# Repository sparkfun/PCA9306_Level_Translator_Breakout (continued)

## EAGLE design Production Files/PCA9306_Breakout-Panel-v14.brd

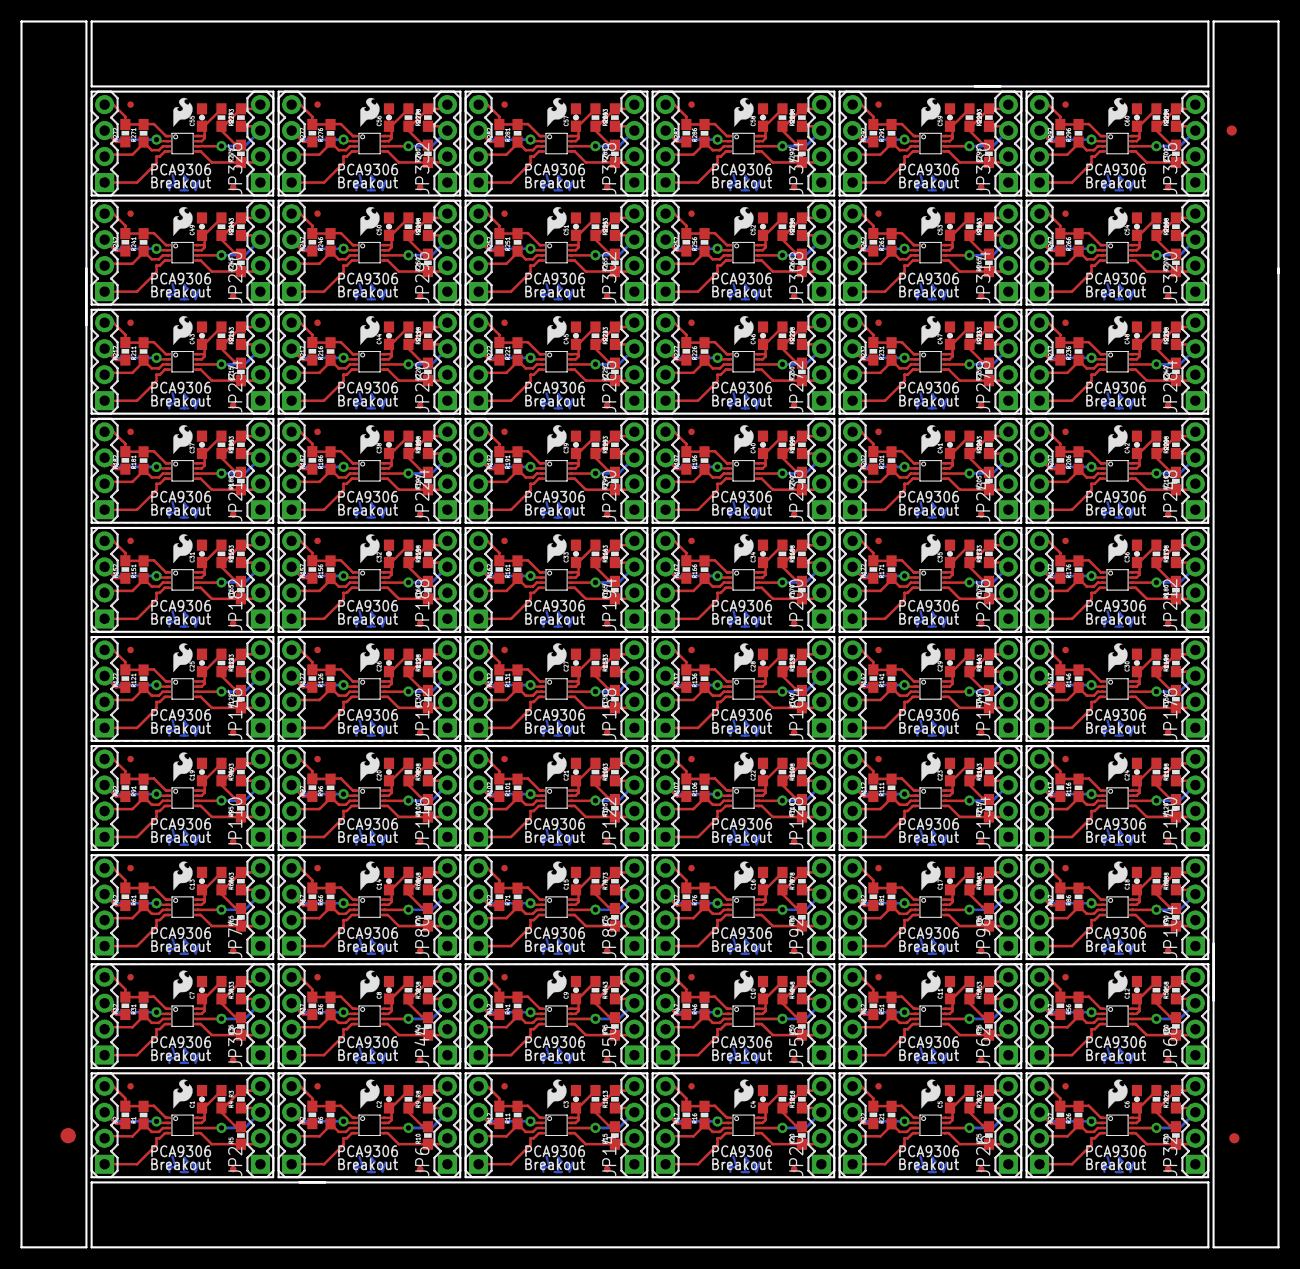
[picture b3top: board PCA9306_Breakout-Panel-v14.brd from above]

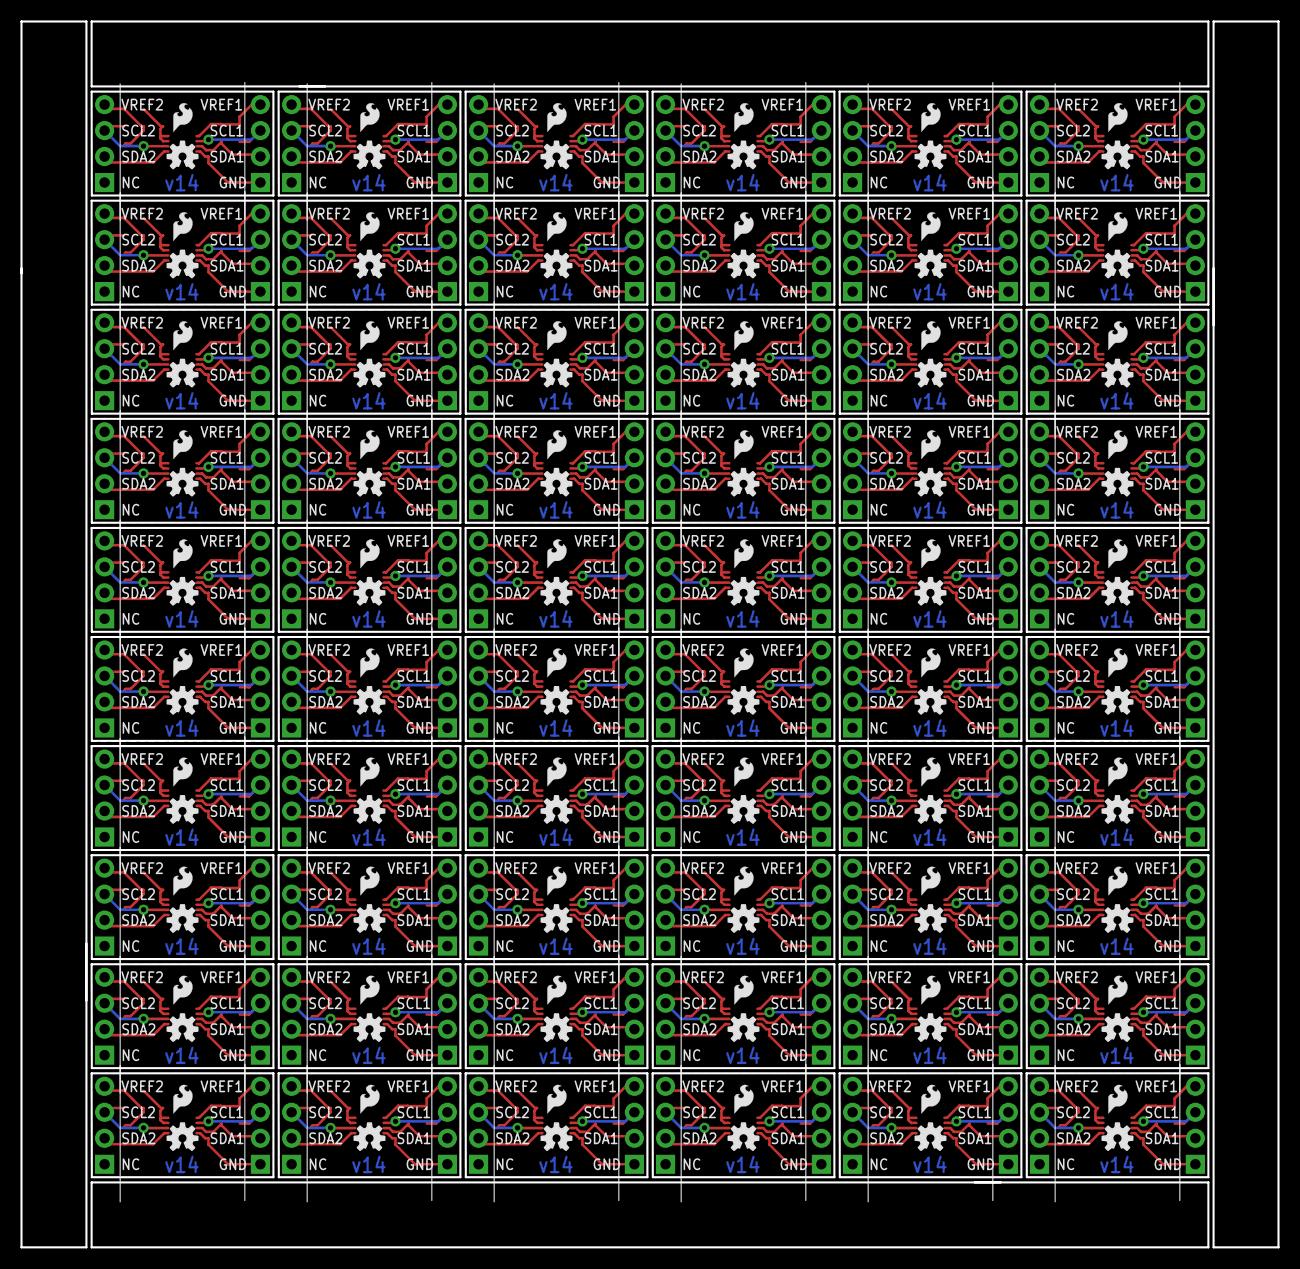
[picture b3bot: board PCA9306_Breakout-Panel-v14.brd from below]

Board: 2 copper layers, 122.9 x 119.9 mm, 843 parts (120 on the bottom side), 480 nets.

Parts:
C1, C2, C3, C4, C5, C6, C7, C8, C9, C10, C11, C12, C13, C14, C15, C16, C17, C18, C19, C20, C21, C22, C23, C24, C25, C26, C27, C28, C29, C30, C31, C32, C33, C34, C35, C36, C37, C38, C39, C40, C41, C42, C43, C44, C45, C46, C47, C48, C49, C50, C51, C52, C53, C54, C55, C56, C57, C58, C59, C60: 0.1uF; 0603-CAP
E$1: FIDUCIAL-1.5X3
E$4, E$5: FIDUCIAL-1X2
JP1, JP2, JP5, JP6, JP13, JP14, JP19, JP20, JP25, JP26, JP31, JP32, JP37, JP38, JP43, JP44, JP49, JP50, JP55, JP56, JP61, JP62, JP67, JP68, JP73, JP74, JP79, JP80, JP85, JP86, JP91, JP92, JP97, JP98, JP103, JP104, JP109, JP110, JP115, JP116, JP121, JP122, JP127, JP128, JP133, JP134, JP139, JP140, JP145, JP146, JP151, JP152, JP157, JP158, JP163, JP164, JP169, JP170, JP175, JP176, JP181, JP182, JP187, JP188, JP193, JP194, JP199, JP200, JP205, JP206, JP211, JP212, JP217, JP218, JP223, JP224, JP229, JP230, JP235, JP236, JP241, JP242, JP247, JP248, JP253, JP254, JP259, JP260, JP265, JP266, JP271, JP272, JP277, JP278, JP283, JP284, JP289, JP290, JP295, JP296, JP301, JP302, JP307, JP308, JP313, JP314, JP319, JP320, JP325, JP326, JP331, JP332, JP337, JP338, JP343, JP344, JP349, JP350, JP355, JP356: 1X04
JP3, JP4, JP9, JP10, JP15, JP16, JP21, JP22, JP27, JP28, JP33, JP34, JP39, JP40, JP45, JP46, JP51, JP52, JP57, JP58, JP63, JP64, JP69, JP70, JP75, JP76, JP81, JP82, JP87, JP88, JP93, JP94, JP99, JP100, JP105, JP106, JP111, JP112, JP117, JP118, JP123, JP124, JP129, JP130, JP135, JP136, JP141, JP142, JP147, JP148, JP153, JP154, JP159, JP160, JP165, JP166, JP171, JP172, JP177, JP178, JP183, JP184, JP189, JP190, JP195, JP196, JP201, JP202, JP207, JP208, JP213, JP214, JP219, JP220, JP225, JP226, JP231, JP232, JP237, JP238, JP243, JP244, JP249, JP250, JP255, JP256, JP261, JP262, JP267, JP268, JP273, JP274, JP279, JP280, JP285, JP286, JP291, JP292, JP297, JP298, JP303, JP304, JP309, JP310, JP315, JP316, JP321, JP322, JP327, JP328, JP333, JP334, JP339, JP340, JP345, JP346, JP351, JP352, JP357, JP358: LOGO-SFESK; SFE-LOGO-FLAME
JP7, JP8, JP11, JP12, JP17, JP18, JP23, JP24, JP29, JP30, JP35, JP36, JP41, JP42, JP47, JP48, JP53, JP54, JP59, JP60, JP65, JP66, JP71, JP72, JP77, JP78, JP83, JP84, JP89, JP90, JP95, JP96, JP101, JP102, JP107, JP108, JP113, JP114, JP119, JP120, JP125, JP126, JP131, JP132, JP137, JP138, JP143, JP144, JP149, JP150, JP155, JP156, JP161, JP162, JP167, JP168, JP173, JP174, JP179, JP180, JP185, JP186, JP191, JP192, JP197, JP198, JP203, JP204, JP209, JP210, JP215, JP216, JP221, JP222, JP227, JP228, JP233, JP234, JP239, JP240, JP245, JP246, JP251, JP252, JP257, JP258, JP263, JP264, JP269, JP270, JP275, JP276, JP281, JP282, JP287, JP288, JP293, JP294, JP299, JP300, JP305, JP306, JP311, JP312, JP317, JP318, JP323, JP324, JP329, JP330, JP335, JP336, JP341, JP342, JP347, JP348, JP353, JP354, JP359, JP360: FIDUCIAL1X2.5; FIDUCIAL-1X2.5
LOGO1, LOGO2, LOGO3, LOGO4, LOGO5, LOGO6, LOGO7, LOGO8, LOGO9, LOGO10, LOGO11, LOGO12, LOGO13, LOGO14, LOGO15, LOGO16, LOGO17, LOGO18, LOGO19, LOGO20, LOGO21, LOGO22, LOGO23, LOGO24, LOGO25, LOGO26, LOGO27, LOGO28, LOGO29, LOGO30, LOGO31, LOGO32, LOGO33, LOGO34, LOGO35, LOGO36, LOGO37, LOGO38, LOGO39, LOGO40, LOGO41, LOGO42, LOGO43, LOGO44, LOGO45, LOGO46, LOGO47, LOGO48, LOGO49, LOGO50, LOGO51, LOGO52, LOGO53, LOGO54, LOGO55, LOGO56, LOGO57, LOGO58, LOGO59, LOGO60: OSHW-LOGOS; OSHW-LOGO-S
R1, R2, R4, R5, R6, R7, R9, R10, R11, R12, R14, R15, R16, R17, R19, R20, R21, R22, R24, R25, R26, R27, R29, R30, R31, R32, R34, R35, R36, R37, R39, R40, R41, R42, R44, R45, R46, R47, R49, R50, R51, R52, R54, R55, R56, R57, R59, R60, R61, R62, R64, R65, R66, R67, R69, R70, R71, R72, R74, R75, R76, R77, R79, R80, R81, R82, R84, R85, R86, R87, R89, R90, R91, R92, R94, R95, R96, R97, R99, R100, R101, R102, R104, R105, R106, R107, R109, R110, R111, R112, R114, R115, R116, R117, R119, R120, R121, R122, R124, R125, R126, R127, R129, R130, R131, R132, R134, R135, R136, R137, R139, R140, R141, R142, R144, R145, R146, R147, R149, R150, R151, R152, R154, R155, R156, R157, R159, R160, R161, R162, R164, R165, R166, R167, R169, R170, R171, R172, R174, R175, R176, R177, R179, R180, R181, R182, R184, R185, R186, R187, R189, R190, R191, R192, R194, R195, R196, R197, R199, R200, R201, R202, R204, R205, R206, R207, R209, R210, R211, R212, R214, R215, R216, R217, R219, R220, R221, R222, R224, R225, R226, R227, R229, R230, R231, R232, R234, R235, R236, R237, R239, R240, R241, R242, R244, R245, R246, R247, R249, R250, R251, R252, R254, R255, R256, R257, R259, R260, R261, R262, R264, R265, R266, R267, R269, R270, R271, R272, R274, R275, R276, R277, R279, R280, R281, R282, R284, R285, R286, R287, R289, R290, R291, R292, R294, R295, R296, R297, R299, R300: 1k; 0603-RES
R3, R8, R13, R18, R23, R28, R33, R38, R43, R48, R53, R58, R63, R68, R73, R78, R83, R88, R93, R98, R103, R108, R113, R118, R123, R128, R133, R138, R143, R148, R153, R158, R163, R168, R173, R178, R183, R188, R193, R198, R203, R208, R213, R218, R223, R228, R233, R238, R243, R248, R253, R258, R263, R268, R273, R278, R283, R288, R293, R298: 200k; 0603-RES
U$1, U$2, U$3, U$4, U$5, U$6, U$7, U$8, U$9, U$10, U$11, U$12, U$13, U$14, U$15, U$16, U$17, U$18, U$19, U$20, U$21, U$22, U$23, U$24, U$25, U$26, U$27, U$28, U$29, U$30, U$31, U$32, U$33, U$34, U$35, U$36, U$37, U$38, U$39, U$40, U$41, U$42, U$43, U$44, U$45, U$46, U$47, U$48, U$49, U$50, U$51, U$52, U$53, U$54, U$55, U$56, U$57, U$58, U$59, U$60: PSOP-8

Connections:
GND: C1.2, JP1.1, U$1.4
GND1: C2.2, JP5.1, U$2.4
GND2: C3.2, JP13.1, U$3.4
GND3: C4.2, JP19.1, U$4.4
GND4: C5.2, JP25.1, U$5.4
GND5: C6.2, JP31.1, U$6.4
GND6: C7.2, JP37.1, U$7.4
GND7: C8.2, JP43.1, U$8.4
GND8: C9.2, JP49.1, U$9.4
GND9: C10.2, JP55.1, U$10.4
GND10: C11.2, JP61.1, U$11.4
GND11: C12.2, JP67.1, U$12.4
GND12: C13.2, JP73.1, U$13.4
GND13: C14.2, JP79.1, U$14.4
GND14: C15.2, JP85.1, U$15.4
GND15: C16.2, JP91.1, U$16.4
GND16: C17.2, JP97.1, U$17.4
GND17: C18.2, JP103.1, U$18.4
GND18: C19.2, JP109.1, U$19.4
GND19: C20.2, JP115.1, U$20.4
GND20: C21.2, JP121.1, U$21.4
GND21: C22.2, JP127.1, U$22.4
GND22: C23.2, JP133.1, U$23.4
GND23: C24.2, JP139.1, U$24.4
GND24: C25.2, JP145.1, U$25.4
GND25: C26.2, JP151.1, U$26.4
GND26: C27.2, JP157.1, U$27.4
GND27: C28.2, JP163.1, U$28.4
GND28: C29.2, JP169.1, U$29.4
GND29: C30.2, JP175.1, U$30.4
GND30: C31.2, JP181.1, U$31.4
GND31: C32.2, JP187.1, U$32.4
GND32: C33.2, JP193.1, U$33.4
GND33: C34.2, JP199.1, U$34.4
GND34: C35.2, JP205.1, U$35.4
GND35: C36.2, JP211.1, U$36.4
GND36: C37.2, JP217.1, U$37.4
GND37: C38.2, JP223.1, U$38.4
GND38: C39.2, JP229.1, U$39.4
GND39: C40.2, JP235.1, U$40.4
GND40: C41.2, JP241.1, U$41.4
GND41: C42.2, JP247.1, U$42.4
GND42: C43.2, JP253.1, U$43.4
GND43: C44.2, JP259.1, U$44.4
GND44: C45.2, JP265.1, U$45.4
GND45: C46.2, JP271.1, U$46.4
GND46: C47.2, JP277.1, U$47.4
GND47: C48.2, JP283.1, U$48.4
GND48: C49.2, JP289.1, U$49.4
GND49: C50.2, JP295.1, U$50.4
GND50: C51.2, JP301.1, U$51.4
GND51: C52.2, JP307.1, U$52.4
GND52: C53.2, JP313.1, U$53.4
GND53: C54.2, JP319.1, U$54.4
GND54: C55.2, JP325.1, U$55.4
GND55: C56.2, JP331.1, U$56.4
GND56: C57.2, JP337.1, U$57.4
GND57: C58.2, JP343.1, U$58.4
GND58: C59.2, JP349.1, U$59.4
GND59: C60.2, JP355.1, U$60.4
SCL1: JP1.3, R2.1, U$1.2
SCL2: JP2.3, R4.1, U$1.6
SCL3: JP5.3, R7.1, U$2.2
SCL4: JP6.3, R9.1, U$2.6
SCL5: JP13.3, R12.1, U$3.2
SCL6: JP14.3, R14.1, U$3.6
SCL7: JP19.3, R17.1, U$4.2
SCL8: JP20.3, R19.1, U$4.6
SCL9: JP25.3, R22.1, U$5.2
SCL10: JP26.3, R24.1, U$5.6
SCL11: JP31.3, R27.1, U$6.2
SCL12: JP32.3, R29.1, U$6.6
SCL13: JP37.3, R32.1, U$7.2
SCL14: JP38.3, R34.1, U$7.6
SCL15: JP43.3, R37.1, U$8.2
SCL16: JP44.3, R39.1, U$8.6
SCL17: JP49.3, R42.1, U$9.2
SCL18: JP50.3, R44.1, U$9.6
SCL19: JP55.3, R47.1, U$10.2
SCL20: JP56.3, R49.1, U$10.6
SCL21: JP61.3, R52.1, U$11.2
SCL22: JP62.3, R54.1, U$11.6
SCL23: JP67.3, R57.1, U$12.2
SCL24: JP68.3, R59.1, U$12.6
SCL25: JP73.3, R62.1, U$13.2
SCL26: JP74.3, R64.1, U$13.6
SCL27: JP79.3, R67.1, U$14.2
SCL28: JP80.3, R69.1, U$14.6
SCL29: JP85.3, R72.1, U$15.2
SCL30: JP86.3, R74.1, U$15.6
SCL31: JP91.3, R77.1, U$16.2
SCL32: JP92.3, R79.1, U$16.6
SCL33: JP97.3, R82.1, U$17.2
SCL34: JP98.3, R84.1, U$17.6
SCL35: JP103.3, R87.1, U$18.2
SCL36: JP104.3, R89.1, U$18.6
SCL37: JP109.3, R92.1, U$19.2
SCL38: JP110.3, R94.1, U$19.6
SCL39: JP115.3, R97.1, U$20.2
SCL40: JP116.3, R99.1, U$20.6
SCL41: JP121.3, R102.1, U$21.2
SCL42: JP122.3, R104.1, U$21.6
SCL43: JP127.3, R107.1, U$22.2
SCL44: JP128.3, R109.1, U$22.6
SCL45: JP133.3, R112.1, U$23.2
SCL46: JP134.3, R114.1, U$23.6
SCL47: JP139.3, R117.1, U$24.2
SCL48: JP140.3, R119.1, U$24.6
SCL49: JP145.3, R122.1, U$25.2
SCL50: JP146.3, R124.1, U$25.6
SCL51: JP151.3, R127.1, U$26.2
SCL52: JP152.3, R129.1, U$26.6
SCL53: JP157.3, R132.1, U$27.2
SCL54: JP158.3, R134.1, U$27.6
SCL55: JP163.3, R137.1, U$28.2
SCL56: JP164.3, R139.1, U$28.6
SCL57: JP169.3, R142.1, U$29.2
SCL58: JP170.3, R144.1, U$29.6
SCL59: JP175.3, R147.1, U$30.2
SCL60: JP176.3, R149.1, U$30.6
SCL61: JP181.3, R152.1, U$31.2
SCL62: JP182.3, R154.1, U$31.6
SCL63: JP187.3, R157.1, U$32.2
SCL64: JP188.3, R159.1, U$32.6
SCL65: JP193.3, R162.1, U$33.2
SCL66: JP194.3, R164.1, U$33.6
SCL67: JP199.3, R167.1, U$34.2
SCL68: JP200.3, R169.1, U$34.6
SCL69: JP205.3, R172.1, U$35.2
SCL70: JP206.3, R174.1, U$35.6
SCL71: JP211.3, R177.1, U$36.2
SCL72: JP212.3, R179.1, U$36.6
SCL73: JP217.3, R182.1, U$37.2
SCL74: JP218.3, R184.1, U$37.6
SCL75: JP223.3, R187.1, U$38.2
SCL76: JP224.3, R189.1, U$38.6
SCL77: JP229.3, R192.1, U$39.2
SCL78: JP230.3, R194.1, U$39.6
SCL79: JP235.3, R197.1, U$40.2
SCL80: JP236.3, R199.1, U$40.6
SCL81: JP241.3, R202.1, U$41.2
SCL82: JP242.3, R204.1, U$41.6
SCL83: JP247.3, R207.1, U$42.2
SCL84: JP248.3, R209.1, U$42.6
SCL85: JP253.3, R212.1, U$43.2
SCL86: JP254.3, R214.1, U$43.6
SCL87: JP259.3, R217.1, U$44.2
SCL88: JP260.3, R219.1, U$44.6
SCL89: JP265.3, R222.1, U$45.2
SCL90: JP266.3, R224.1, U$45.6
SCL91: JP271.3, R227.1, U$46.2
SCL92: JP272.3, R229.1, U$46.6
SCL93: JP277.3, R232.1, U$47.2
SCL94: JP278.3, R234.1, U$47.6
SCL95: JP283.3, R237.1, U$48.2
SCL96: JP284.3, R239.1, U$48.6
SCL97: JP289.3, R242.1, U$49.2
SCL98: JP290.3, R244.1, U$49.6
SCL99: JP295.3, R247.1, U$50.2
SCL100: JP296.3, R249.1, U$50.6
SCL101: JP301.3, R252.1, U$51.2
SCL102: JP302.3, R254.1, U$51.6
SCL103: JP307.3, R257.1, U$52.2
SCL104: JP308.3, R259.1, U$52.6
SCL105: JP313.3, R262.1, U$53.2
SCL106: JP314.3, R264.1, U$53.6
SCL107: JP319.3, R267.1, U$54.2
SCL108: JP320.3, R269.1, U$54.6
SCL109: JP325.3, R272.1, U$55.2
SCL110: JP326.3, R274.1, U$55.6
SCL111: JP331.3, R277.1, U$56.2
SCL112: JP332.3, R279.1, U$56.6
SCL113: JP337.3, R282.1, U$57.2
SCL114: JP338.3, R284.1, U$57.6
SCL115: JP343.3, R287.1, U$58.2
SCL116: JP344.3, R289.1, U$58.6
SCL117: JP349.3, R292.1, U$59.2
SCL118: JP350.3, R294.1, U$59.6
SCL119: JP355.3, R297.1, U$60.2
SCL120: JP356.3, R299.1, U$60.6
SDA1: JP1.2, R1.1, U$1.3
SDA2: JP2.2, R5.1, U$1.5
SDA3: JP5.2, R6.1, U$2.3
SDA4: JP6.2, R10.1, U$2.5
SDA5: JP13.2, R11.1, U$3.3
SDA6: JP14.2, R15.1, U$3.5
SDA7: JP19.2, R16.1, U$4.3
SDA8: JP20.2, R20.1, U$4.5
SDA9: JP25.2, R21.1, U$5.3
SDA10: JP26.2, R25.1, U$5.5
SDA11: JP31.2, R26.1, U$6.3
SDA12: JP32.2, R30.1, U$6.5
SDA13: JP37.2, R31.1, U$7.3
SDA14: JP38.2, R35.1, U$7.5
SDA15: JP43.2, R36.1, U$8.3
SDA16: JP44.2, R40.1, U$8.5
SDA17: JP49.2, R41.1, U$9.3
SDA18: JP50.2, R45.1, U$9.5
SDA19: JP55.2, R46.1, U$10.3
SDA20: JP56.2, R50.1, U$10.5
SDA21: JP61.2, R51.1, U$11.3
SDA22: JP62.2, R55.1, U$11.5
SDA23: JP67.2, R56.1, U$12.3
SDA24: JP68.2, R60.1, U$12.5
SDA25: JP73.2, R61.1, U$13.3
SDA26: JP74.2, R65.1, U$13.5
SDA27: JP79.2, R66.1, U$14.3
SDA28: JP80.2, R70.1, U$14.5
SDA29: JP85.2, R71.1, U$15.3
SDA30: JP86.2, R75.1, U$15.5
SDA31: JP91.2, R76.1, U$16.3
SDA32: JP92.2, R80.1, U$16.5
SDA33: JP97.2, R81.1, U$17.3
SDA34: JP98.2, R85.1, U$17.5
SDA35: JP103.2, R86.1, U$18.3
SDA36: JP104.2, R90.1, U$18.5
SDA37: JP109.2, R91.1, U$19.3
SDA38: JP110.2, R95.1, U$19.5
SDA39: JP115.2, R96.1, U$20.3
SDA40: JP116.2, R100.1, U$20.5
SDA41: JP121.2, R101.1, U$21.3
SDA42: JP122.2, R105.1, U$21.5
SDA43: JP127.2, R106.1, U$22.3
SDA44: JP128.2, R110.1, U$22.5
SDA45: JP133.2, R111.1, U$23.3
SDA46: JP134.2, R115.1, U$23.5
SDA47: JP139.2, R116.1, U$24.3
SDA48: JP140.2, R120.1, U$24.5
SDA49: JP145.2, R121.1, U$25.3
SDA50: JP146.2, R125.1, U$25.5
SDA51: JP151.2, R126.1, U$26.3
SDA52: JP152.2, R130.1, U$26.5
SDA53: JP157.2, R131.1, U$27.3
SDA54: JP158.2, R135.1, U$27.5
SDA55: JP163.2, R136.1, U$28.3
SDA56: JP164.2, R140.1, U$28.5
SDA57: JP169.2, R141.1, U$29.3
SDA58: JP170.2, R145.1, U$29.5
SDA59: JP175.2, R146.1, U$30.3
SDA60: JP176.2, R150.1, U$30.5
SDA61: JP181.2, R151.1, U$31.3
SDA62: JP182.2, R155.1, U$31.5
SDA63: JP187.2, R156.1, U$32.3
SDA64: JP188.2, R160.1, U$32.5
SDA65: JP193.2, R161.1, U$33.3
SDA66: JP194.2, R165.1, U$33.5
SDA67: JP199.2, R166.1, U$34.3
SDA68: JP200.2, R170.1, U$34.5
SDA69: JP205.2, R171.1, U$35.3
SDA70: JP206.2, R175.1, U$35.5
SDA71: JP211.2, R176.1, U$36.3
SDA72: JP212.2, R180.1, U$36.5
SDA73: JP217.2, R181.1, U$37.3
SDA74: JP218.2, R185.1, U$37.5
SDA75: JP223.2, R186.1, U$38.3
SDA76: JP224.2, R190.1, U$38.5
SDA77: JP229.2, R191.1, U$39.3
SDA78: JP230.2, R195.1, U$39.5
SDA79: JP235.2, R196.1, U$40.3
SDA80: JP236.2, R200.1, U$40.5
SDA81: JP241.2, R201.1, U$41.3
SDA82: JP242.2, R205.1, U$41.5
SDA83: JP247.2, R206.1, U$42.3
SDA84: JP248.2, R210.1, U$42.5
SDA85: JP253.2, R211.1, U$43.3
SDA86: JP254.2, R215.1, U$43.5
SDA87: JP259.2, R216.1, U$44.3
SDA88: JP260.2, R220.1, U$44.5
SDA89: JP265.2, R221.1, U$45.3
SDA90: JP266.2, R225.1, U$45.5
SDA91: JP271.2, R226.1, U$46.3
SDA92: JP272.2, R230.1, U$46.5
SDA93: JP277.2, R231.1, U$47.3
SDA94: JP278.2, R235.1, U$47.5
SDA95: JP283.2, R236.1, U$48.3
SDA96: JP284.2, R240.1, U$48.5
SDA97: JP289.2, R241.1, U$49.3
SDA98: JP290.2, R245.1, U$49.5
SDA99: JP295.2, R246.1, U$50.3
SDA100: JP296.2, R250.1, U$50.5
SDA101: JP301.2, R251.1, U$51.3
SDA102: JP302.2, R255.1, U$51.5
SDA103: JP307.2, R256.1, U$52.3
SDA104: JP308.2, R260.1, U$52.5
SDA105: JP313.2, R261.1, U$53.3
SDA106: JP314.2, R265.1, U$53.5
SDA107: JP319.2, R266.1, U$54.3
SDA108: JP320.2, R270.1, U$54.5
SDA109: JP325.2, R271.1, U$55.3
SDA110: JP326.2, R275.1, U$55.5
SDA111: JP331.2, R276.1, U$56.3
SDA112: JP332.2, R280.1, U$56.5
SDA113: JP337.2, R281.1, U$57.3
SDA114: JP338.2, R285.1, U$57.5
SDA115: JP343.2, R286.1, U$58.3
SDA116: JP344.2, R290.1, U$58.5
SDA117: JP349.2, R291.1, U$59.3
SDA118: JP350.2, R295.1, U$59.5
SDA119: JP355.2, R296.1, U$60.3
SDA120: JP356.2, R300.1, U$60.5
VREF1: JP1.4, R1.2, R2.2, U$1.1
VREF2: C1.1, R3.1, U$1.7, U$1.8
VREF3: JP5.4, R6.2, R7.2, U$2.1
VREF4: C2.1, R8.1, U$2.7, U$2.8
VREF5: JP13.4, R11.2, R12.2, U$3.1
VREF6: C3.1, R13.1, U$3.7, U$3.8
VREF7: JP19.4, R16.2, R17.2, U$4.1
VREF8: C4.1, R18.1, U$4.7, U$4.8
VREF9: JP25.4, R21.2, R22.2, U$5.1
VREF10: C5.1, R23.1, U$5.7, U$5.8
VREF11: JP31.4, R26.2, R27.2, U$6.1
VREF12: C6.1, R28.1, U$6.7, U$6.8
VREF13: JP37.4, R31.2, R32.2, U$7.1
VREF14: C7.1, R33.1, U$7.7, U$7.8
VREF15: JP43.4, R36.2, R37.2, U$8.1
VREF16: C8.1, R38.1, U$8.7, U$8.8
VREF17: JP49.4, R41.2, R42.2, U$9.1
VREF18: C9.1, R43.1, U$9.7, U$9.8
VREF19: JP55.4, R46.2, R47.2, U$10.1
VREF20: C10.1, R48.1, U$10.7, U$10.8
VREF21: JP61.4, R51.2, R52.2, U$11.1
VREF22: C11.1, R53.1, U$11.7, U$11.8
VREF23: JP67.4, R56.2, R57.2, U$12.1
VREF24: C12.1, R58.1, U$12.7, U$12.8
VREF25: JP73.4, R61.2, R62.2, U$13.1
VREF26: C13.1, R63.1, U$13.7, U$13.8
VREF27: JP79.4, R66.2, R67.2, U$14.1
VREF28: C14.1, R68.1, U$14.7, U$14.8
VREF29: JP85.4, R71.2, R72.2, U$15.1
VREF30: C15.1, R73.1, U$15.7, U$15.8
VREF31: JP91.4, R76.2, R77.2, U$16.1
VREF32: C16.1, R78.1, U$16.7, U$16.8
VREF33: JP97.4, R81.2, R82.2, U$17.1
VREF34: C17.1, R83.1, U$17.7, U$17.8
VREF35: JP103.4, R86.2, R87.2, U$18.1
VREF36: C18.1, R88.1, U$18.7, U$18.8
VREF37: JP109.4, R91.2, R92.2, U$19.1
VREF38: C19.1, R93.1, U$19.7, U$19.8
VREF39: JP115.4, R96.2, R97.2, U$20.1
VREF40: C20.1, R98.1, U$20.7, U$20.8
VREF41: JP121.4, R101.2, R102.2, U$21.1
VREF42: C21.1, R103.1, U$21.7, U$21.8
VREF43: JP127.4, R106.2, R107.2, U$22.1
VREF44: C22.1, R108.1, U$22.7, U$22.8
VREF45: JP133.4, R111.2, R112.2, U$23.1
VREF46: C23.1, R113.1, U$23.7, U$23.8
VREF47: JP139.4, R116.2, R117.2, U$24.1
VREF48: C24.1, R118.1, U$24.7, U$24.8
VREF49: JP145.4, R121.2, R122.2, U$25.1
VREF50: C25.1, R123.1, U$25.7, U$25.8
VREF51: JP151.4, R126.2, R127.2, U$26.1
VREF52: C26.1, R128.1, U$26.7, U$26.8
VREF53: JP157.4, R131.2, R132.2, U$27.1
VREF54: C27.1, R133.1, U$27.7, U$27.8
VREF55: JP163.4, R136.2, R137.2, U$28.1
VREF56: C28.1, R138.1, U$28.7, U$28.8
VREF57: JP169.4, R141.2, R142.2, U$29.1
VREF58: C29.1, R143.1, U$29.7, U$29.8
VREF59: JP175.4, R146.2, R147.2, U$30.1
VREF60: C30.1, R148.1, U$30.7, U$30.8
VREF61: JP181.4, R151.2, R152.2, U$31.1
VREF62: C31.1, R153.1, U$31.7, U$31.8
VREF63: JP187.4, R156.2, R157.2, U$32.1
VREF64: C32.1, R158.1, U$32.7, U$32.8
VREF65: JP193.4, R161.2, R162.2, U$33.1
VREF66: C33.1, R163.1, U$33.7, U$33.8
VREF67: JP199.4, R166.2, R167.2, U$34.1
VREF68: C34.1, R168.1, U$34.7, U$34.8
VREF69: JP205.4, R171.2, R172.2, U$35.1
VREF70: C35.1, R173.1, U$35.7, U$35.8
VREF71: JP211.4, R176.2, R177.2, U$36.1
VREF72: C36.1, R178.1, U$36.7, U$36.8
VREF73: JP217.4, R181.2, R182.2, U$37.1
VREF74: C37.1, R183.1, U$37.7, U$37.8
VREF75: JP223.4, R186.2, R187.2, U$38.1
VREF76: C38.1, R188.1, U$38.7, U$38.8
VREF77: JP229.4, R191.2, R192.2, U$39.1
VREF78: C39.1, R193.1, U$39.7, U$39.8
VREF79: JP235.4, R196.2, R197.2, U$40.1
VREF80: C40.1, R198.1, U$40.7, U$40.8
VREF81: JP241.4, R201.2, R202.2, U$41.1
VREF82: C41.1, R203.1, U$41.7, U$41.8
VREF83: JP247.4, R206.2, R207.2, U$42.1
VREF84: C42.1, R208.1, U$42.7, U$42.8
VREF85: JP253.4, R211.2, R212.2, U$43.1
VREF86: C43.1, R213.1, U$43.7, U$43.8
VREF87: JP259.4, R216.2, R217.2, U$44.1
VREF88: C44.1, R218.1, U$44.7, U$44.8
VREF89: JP265.4, R221.2, R222.2, U$45.1
VREF90: C45.1, R223.1, U$45.7, U$45.8
VREF91: JP271.4, R226.2, R227.2, U$46.1
VREF92: C46.1, R228.1, U$46.7, U$46.8
VREF93: JP277.4, R231.2, R232.2, U$47.1
VREF94: C47.1, R233.1, U$47.7, U$47.8
VREF95: JP283.4, R236.2, R237.2, U$48.1
VREF96: C48.1, R238.1, U$48.7, U$48.8
VREF97: JP289.4, R241.2, R242.2, U$49.1
VREF98: C49.1, R243.1, U$49.7, U$49.8
VREF99: JP295.4, R246.2, R247.2, U$50.1
VREF100: C50.1, R248.1, U$50.7, U$50.8
VREF101: JP301.4, R251.2, R252.2, U$51.1
VREF102: C51.1, R253.1, U$51.7, U$51.8
VREF103: JP307.4, R256.2, R257.2, U$52.1
VREF104: C52.1, R258.1, U$52.7, U$52.8
VREF105: JP313.4, R261.2, R262.2, U$53.1
VREF106: C53.1, R263.1, U$53.7, U$53.8
VREF107: JP319.4, R266.2, R267.2, U$54.1
VREF108: C54.1, R268.1, U$54.7, U$54.8
VREF109: JP325.4, R271.2, R272.2, U$55.1
VREF110: C55.1, R273.1, U$55.7, U$55.8
VREF111: JP331.4, R276.2, R277.2, U$56.1
VREF112: C56.1, R278.1, U$56.7, U$56.8
VREF113: JP337.4, R281.2, R282.2, U$57.1
VREF114: C57.1, R283.1, U$57.7, U$57.8
VREF115: JP343.4, R286.2, R287.2, U$58.1
VREF116: C58.1, R288.1, U$58.7, U$58.8
VREF117: JP349.4, R291.2, R292.2, U$59.1
VREF118: C59.1, R293.1, U$59.7, U$59.8
VREF119: JP355.4, R296.2, R297.2, U$60.1
VREF120: C60.1, R298.1, U$60.7, U$60.8
VREF_1: JP6.4, R8.2, R9.2, R10.2
VREF_2: JP2.4, R3.2, R4.2, R5.2
VREF_3: JP14.4, R13.2, R14.2, R15.2
VREF_4: JP20.4, R18.2, R19.2, R20.2
VREF_5: JP26.4, R23.2, R24.2, R25.2
VREF_6: JP32.4, R28.2, R29.2, R30.2
VREF_7: JP38.4, R33.2, R34.2, R35.2
VREF_8: JP44.4, R38.2, R39.2, R40.2
VREF_9: JP50.4, R43.2, R44.2, R45.2
VREF_10: JP56.4, R48.2, R49.2, R50.2
VREF_11: JP62.4, R53.2, R54.2, R55.2
VREF_12: JP68.4, R58.2, R59.2, R60.2
VREF_13: JP74.4, R63.2, R64.2, R65.2
VREF_14: JP80.4, R68.2, R69.2, R70.2
VREF_15: JP86.4, R73.2, R74.2, R75.2
VREF_16: JP92.4, R78.2, R79.2, R80.2
VREF_17: JP98.4, R83.2, R84.2, R85.2
VREF_18: JP104.4, R88.2, R89.2, R90.2
VREF_19: JP110.4, R93.2, R94.2, R95.2
VREF_20: JP116.4, R98.2, R99.2, R100.2
VREF_21: JP122.4, R103.2, R104.2, R105.2
VREF_22: JP128.4, R108.2, R109.2, R110.2
VREF_23: JP134.4, R113.2, R114.2, R115.2
VREF_24: JP140.4, R118.2, R119.2, R120.2
VREF_25: JP146.4, R123.2, R124.2, R125.2
VREF_26: JP152.4, R128.2, R129.2, R130.2
VREF_27: JP158.4, R133.2, R134.2, R135.2
VREF_28: JP164.4, R138.2, R139.2, R140.2
VREF_29: JP170.4, R143.2, R144.2, R145.2
VREF_30: JP176.4, R148.2, R149.2, R150.2
VREF_31: JP182.4, R153.2, R154.2, R155.2
VREF_32: JP188.4, R158.2, R159.2, R160.2
VREF_33: JP194.4, R163.2, R164.2, R165.2
VREF_34: JP200.4, R168.2, R169.2, R170.2
VREF_35: JP206.4, R173.2, R174.2, R175.2
VREF_36: JP212.4, R178.2, R179.2, R180.2
VREF_37: JP218.4, R183.2, R184.2, R185.2
VREF_38: JP224.4, R188.2, R189.2, R190.2
VREF_39: JP230.4, R193.2, R194.2, R195.2
VREF_40: JP236.4, R198.2, R199.2, R200.2
VREF_41: JP242.4, R203.2, R204.2, R205.2
VREF_42: JP248.4, R208.2, R209.2, R210.2
VREF_43: JP254.4, R213.2, R214.2, R215.2
VREF_44: JP260.4, R218.2, R219.2, R220.2
VREF_45: JP266.4, R223.2, R224.2, R225.2
VREF_46: JP272.4, R228.2, R229.2, R230.2
VREF_47: JP278.4, R233.2, R234.2, R235.2
VREF_48: JP284.4, R238.2, R239.2, R240.2
VREF_49: JP290.4, R243.2, R244.2, R245.2
VREF_50: JP296.4, R248.2, R249.2, R250.2
VREF_51: JP302.4, R253.2, R254.2, R255.2
VREF_52: JP308.4, R258.2, R259.2, R260.2
VREF_53: JP314.4, R263.2, R264.2, R265.2
VREF_54: JP320.4, R268.2, R269.2, R270.2
VREF_55: JP326.4, R273.2, R274.2, R275.2
VREF_56: JP332.4, R278.2, R279.2, R280.2
VREF_57: JP338.4, R283.2, R284.2, R285.2
VREF_58: JP344.4, R288.2, R289.2, R290.2
VREF_59: JP350.4, R293.2, R294.2, R295.2
VREF_60: JP356.4, R298.2, R299.2, R300.2

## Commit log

2013-06-04 Updated README and revised board files to v14
2013-06-04 Update README.md
    Fixed image URL.
2013-06-11 Rerouted traces away from IC and changed packages to 0603. Add labels to the schematic on the header pins.
2013-07-03 Updating layout
2013-07-03 Fixed font size on schematic labels.
2013-07-08 Production ready v14
    created panel
2013-08-29 Checking 1:1 FP on IC
2013-10-02 Panel Created
2019-06-04 Documentation added for v20
2019-06-11 Adds slik lables, adds jumper for enable pin, increases size by 10 mils in both x and y direction, updates PCA9306 to new package
2019-06-12 Adds an additional PTH header for GND on VREF2 side
2019-06-13 Moves Open Hardware symbol
2019-06-13 Moves passives to lower half of board, resulting in full retrace of board....
    *Adds HIGH/LOW silk to board
    *Adds triple jumper to correctly add enable feature
    *Changes 0.1uF capacitor to 100pF capacitor
2019-06-14 Updates silk on jumper and "HIGH" and "LOW" voltages on bottom, renumbers parts in schematic
2019-06-17 Fixes traces for both data lines, corrects punctuation of schematic note.
2019-06-17 Updates SKU for new level translator
2019-06-17 Removes randome script file
2019-06-17 Changes version number to v20
2019-06-17 Changes name of board files ONLY
2019-06-17 Changes label to "Switch" rather than shorthand "Swch"
2019-06-17 Adds production files
2019-07-18 Updates enable text in schematic
